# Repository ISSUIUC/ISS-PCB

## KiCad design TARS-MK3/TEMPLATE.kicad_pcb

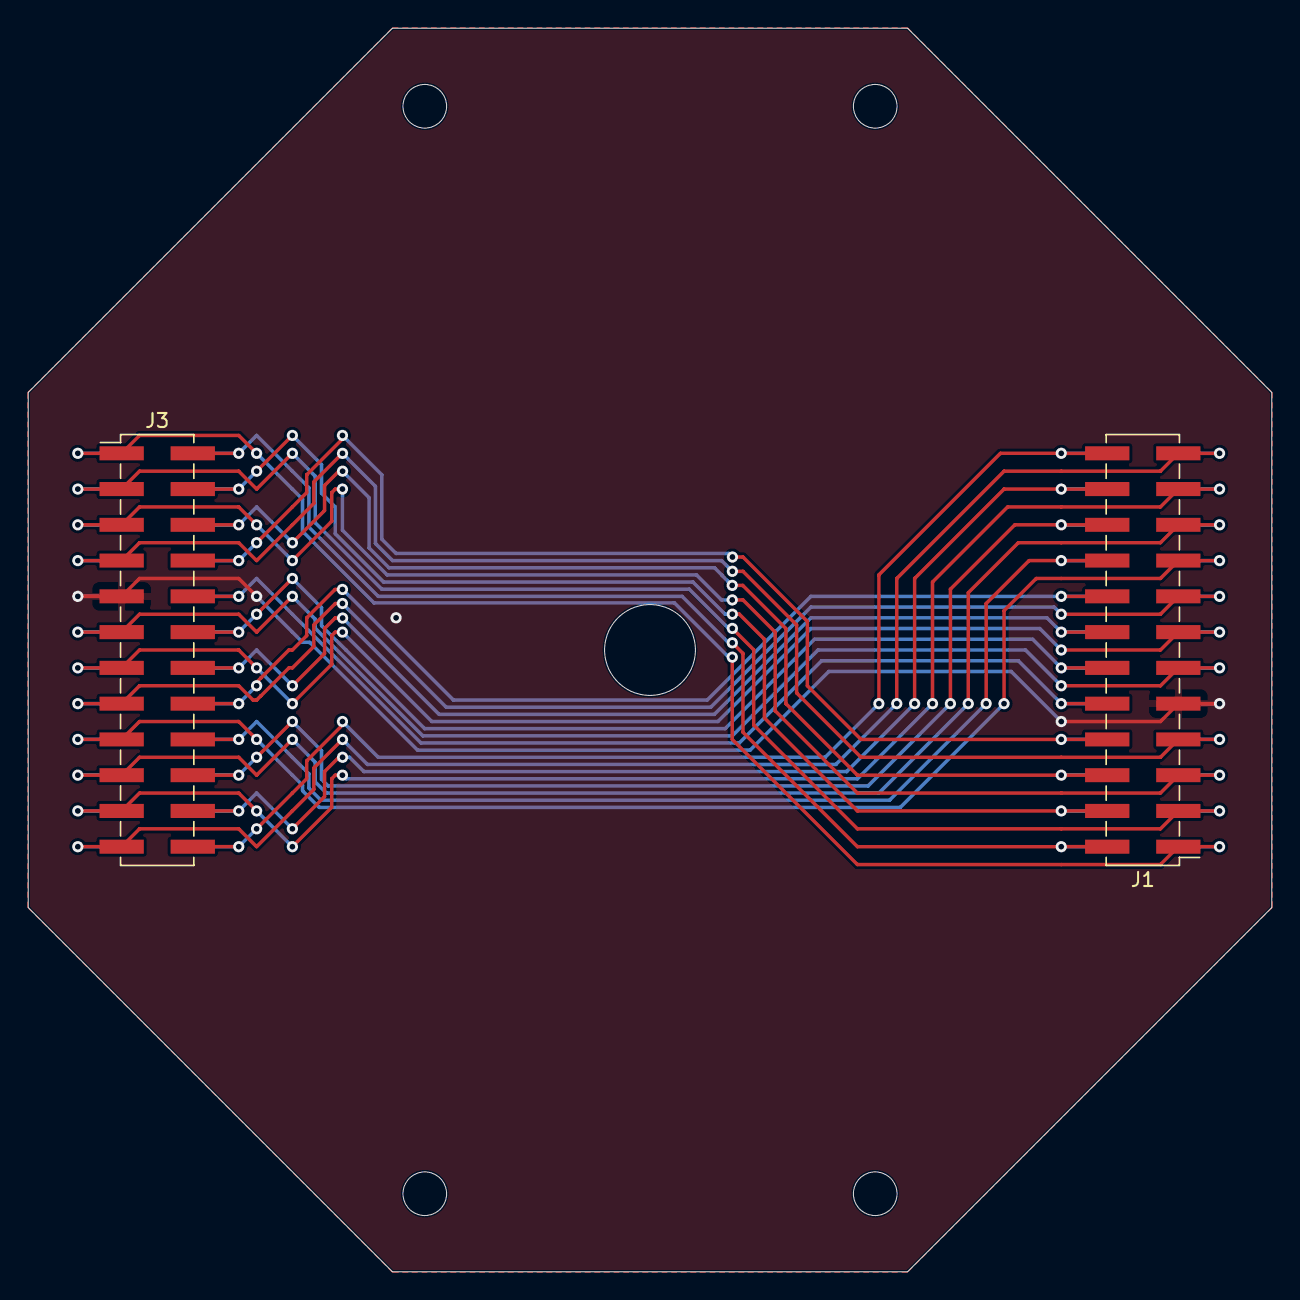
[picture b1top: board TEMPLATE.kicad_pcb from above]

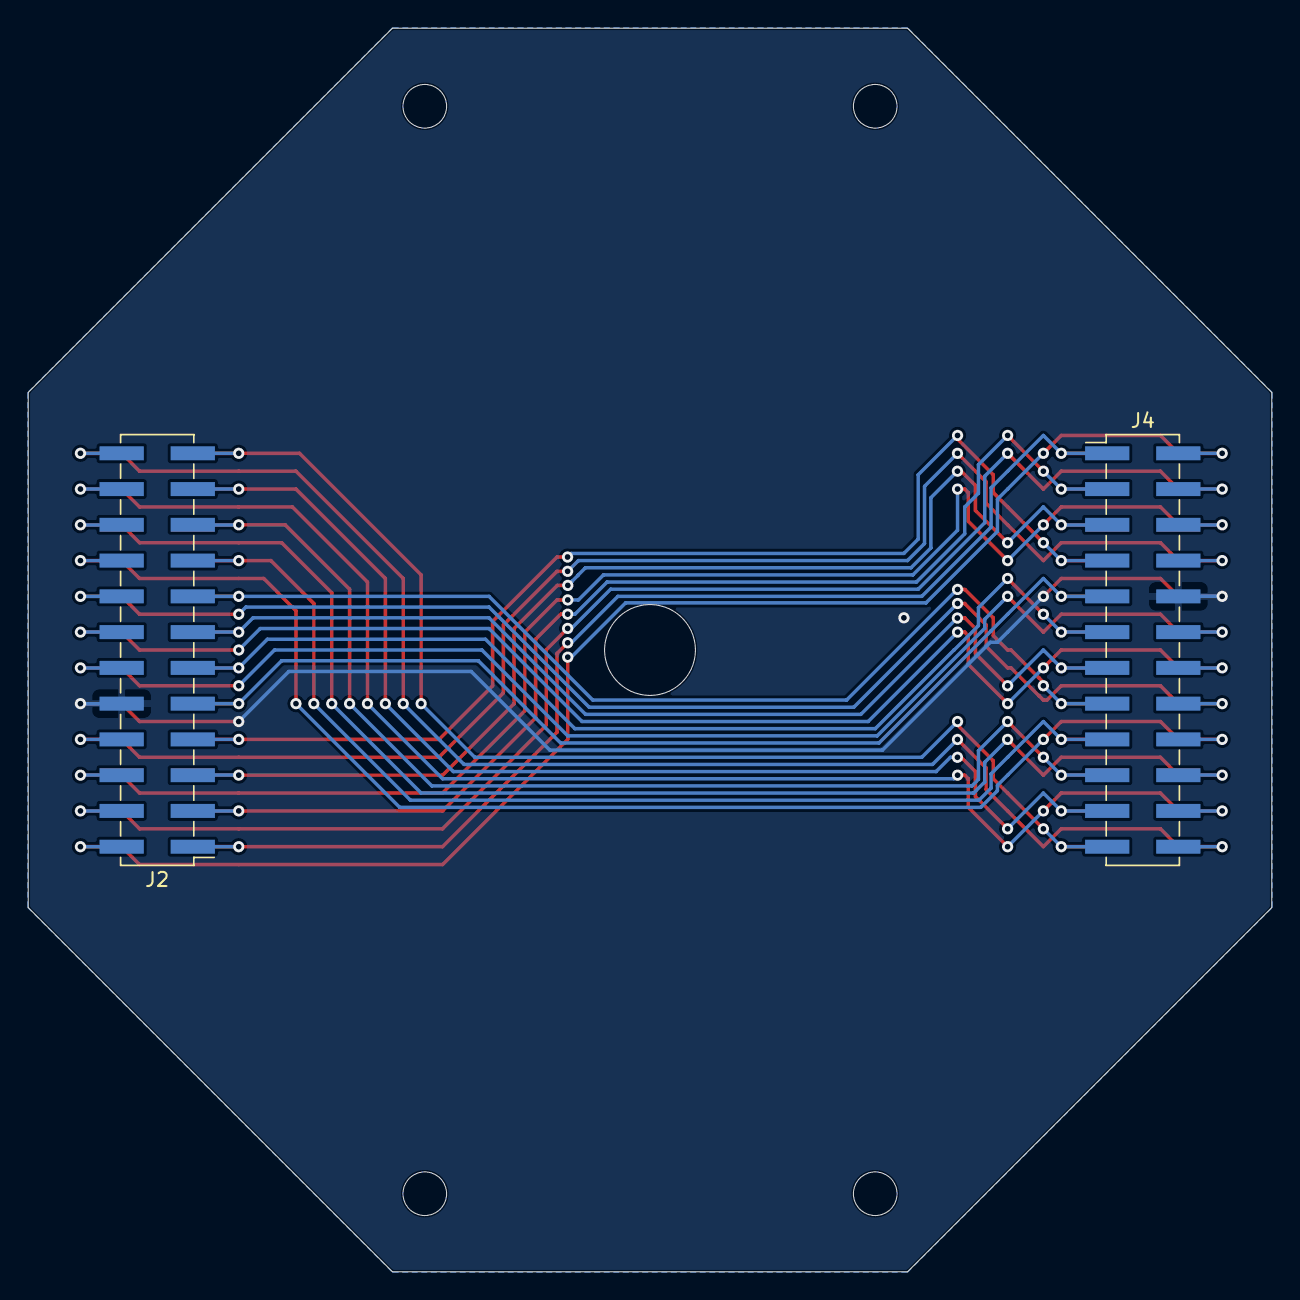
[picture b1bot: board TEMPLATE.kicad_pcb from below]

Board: 2 copper layers, 88.3 x 88.3 mm, 4 parts (2 on the bottom side), 24 nets.

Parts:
J1, J2, J3, J4: Conn_02x12_Odd_Even; PinHeader_2x12_P2.54mm_Vertical_SMD

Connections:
/3V3: J1.7, J2.8, J3.7, J4.8
/5V: J1.5, J2.6, J3.5, J4.6
/9V: J1.3, J2.4, J3.3, J4.4
/B2B_GPIO_0: J1.2, J2.1, J3.2, J4.1
/B2B_GPIO_1: J1.4, J2.3, J3.4, J4.3
/B2B_GPIO_2: J1.6, J2.5, J3.6, J4.5
/B2B_GPIO_3: J1.8, J2.7, J3.8, J4.7
/B2B_GPIO_4: J1.10, J2.9, J3.10, J4.9
/B2B_GPIO_5: J1.12, J2.11, J3.12, J4.11
/B2B_GPIO_6: J1.14, J2.13, J3.14, J4.13
/B2B_GPIO_7: J1.16, J2.15, J3.16, J4.15
/B2B_GPIO_8: J1.18, J2.17, J3.18, J4.17
/B2B_GPIO_9: J1.20, J2.19, J3.20, J4.19
/B2B_GPIO_10: J1.22, J2.21, J3.22, J4.21
/B2B_GPIO_11: J1.24, J2.23, J3.24, J4.23
/B2B_I2C_SCL: J1.17, J2.18, J3.17, J4.18
/B2B_I2C_SDA: J1.15, J2.16, J3.15, J4.16
/B2B_SPI_MISO: J1.21, J2.22, J3.21, J4.22
/B2B_SPI_MOSI: J1.23, J2.24, J3.23, J4.24
/B2B_SPI_SCK: J1.19, J2.20, J3.19, J4.20
/B2B_UART_RX: J1.11, J2.12, J3.11, J4.12
/B2B_UART_TX: J1.13, J2.14, J3.13, J4.14
/GND: J1.9, J2.10, J3.9, J4.10
/VBAT: J1.1, J2.2, J3.1, J4.2

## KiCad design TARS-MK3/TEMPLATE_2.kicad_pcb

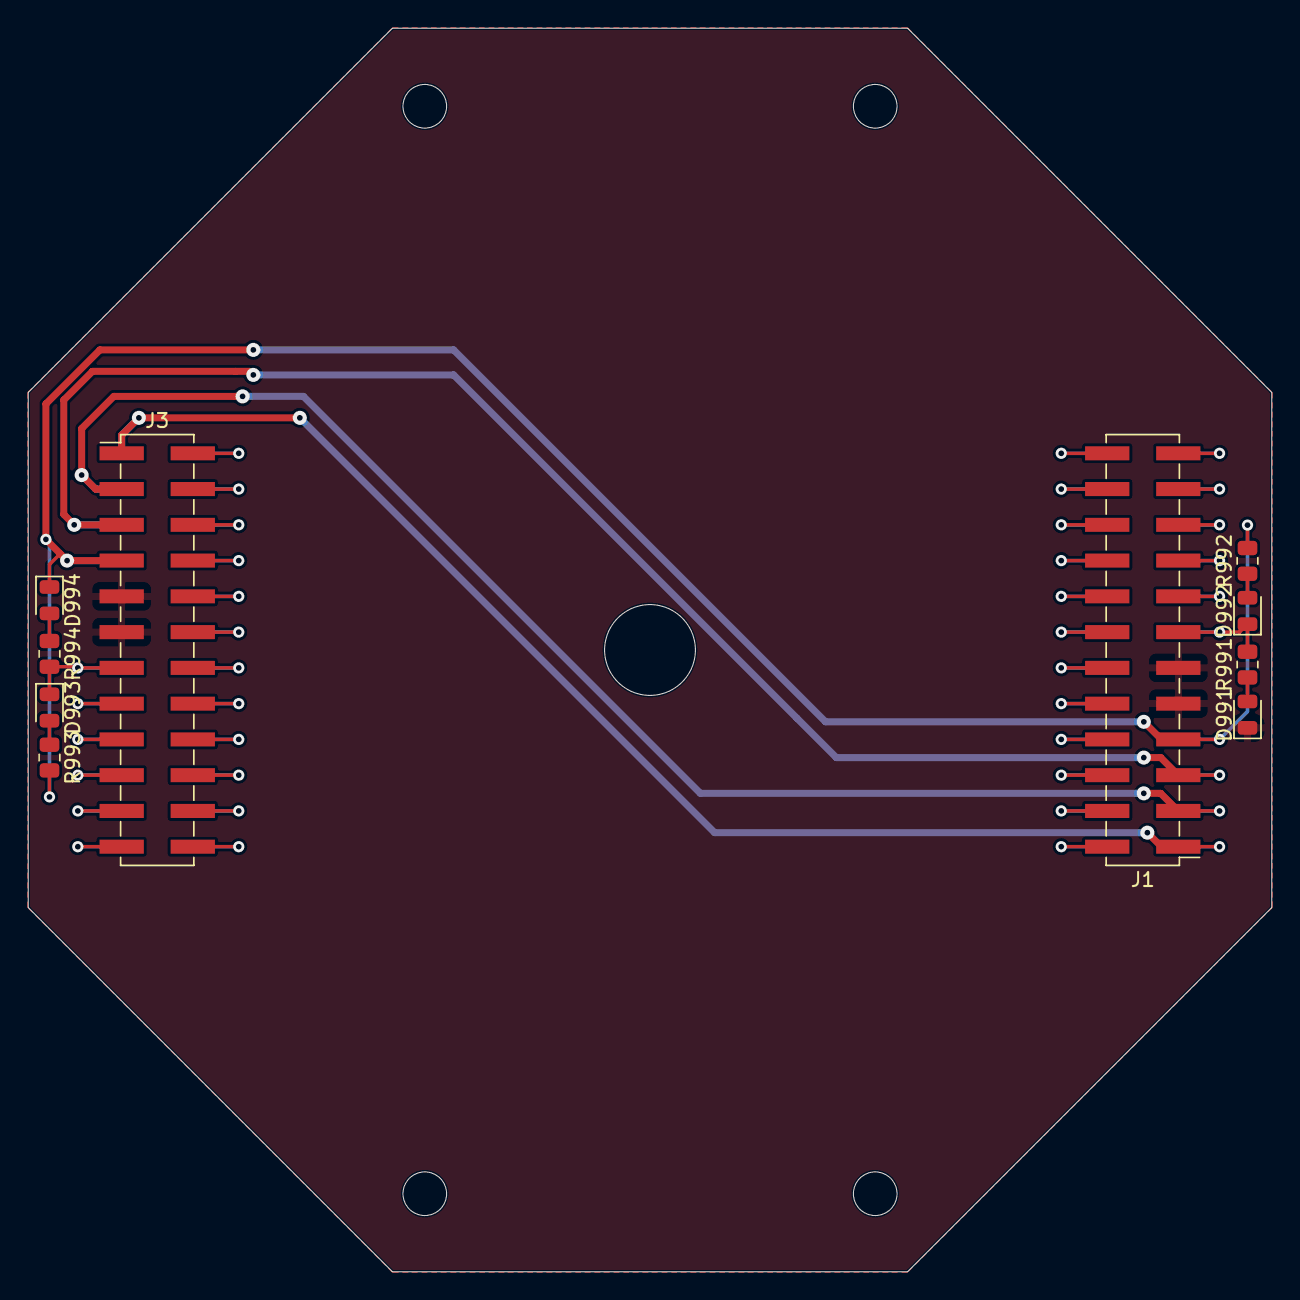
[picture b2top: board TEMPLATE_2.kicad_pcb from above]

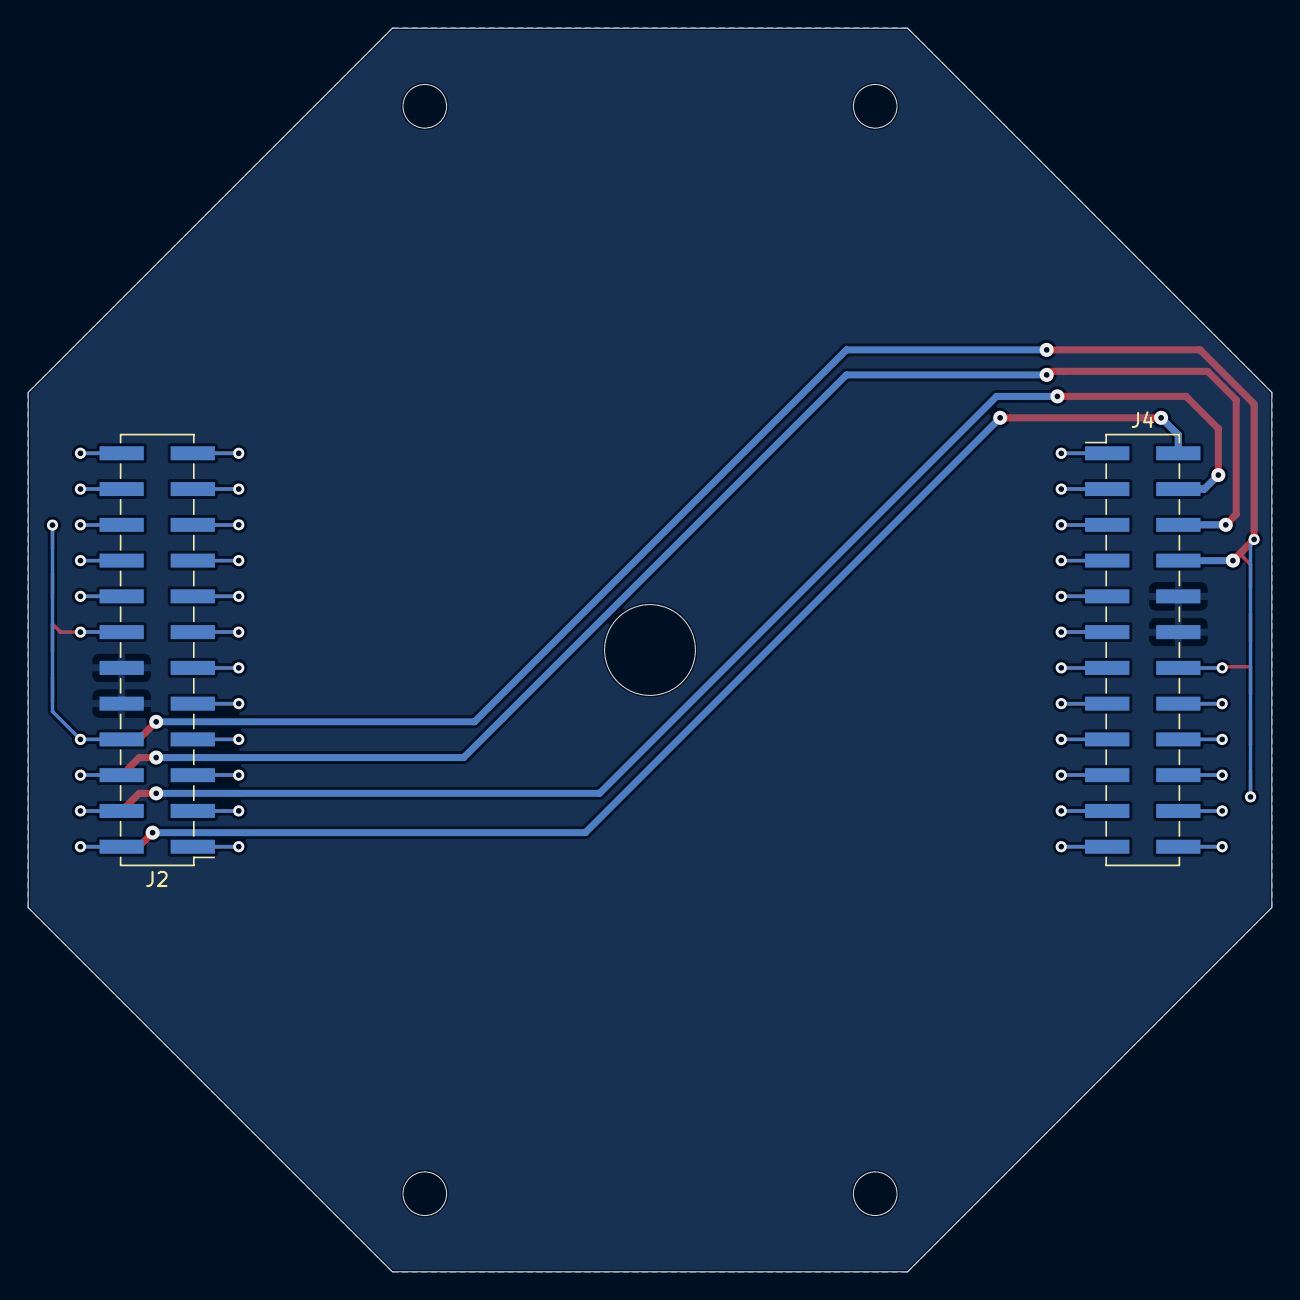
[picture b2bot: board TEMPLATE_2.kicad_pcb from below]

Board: 2 copper layers, 88.3 x 88.3 mm, 12 parts (2 on the bottom side), 45 nets.

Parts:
D991, D993: GREEN; LED_0805_2012Metric
D992, D994: RED; LED_0805_2012Metric
J1, J2, J3, J4: Conn_02x12_Odd_Even; PinHeader_2x12_P2.54mm_Vertical_SMD
R991, R992, R993, R994: 270Ohm; R_0805_2012Metric

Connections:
/3V3: D994.1 (K), J1.7, J2.8, J3.7, J4.8, R992.2, R993.2
/5V: J1.5, J2.6, J3.5, J4.6
/9V: J1.3, J2.4, J3.3, J4.4
/B2B_GPIO_0: J1.16, J2.15
/B2B_GPIO_1: J1.18, J2.17
/B2B_GPIO_2: J1.20, J2.19
/B2B_GPIO_3: J1.22, J2.21
/B2B_GPIO_4: J1.24, J2.23
/B2B_GPIO_5: J3.15, J4.16
/B2B_GPIO_6: J3.17, J4.18
/B2B_GPIO_7: J3.19, J4.20
/B2B_GPIO_8: J3.21, J4.22
/B2B_GPIO_9: J3.23, J4.24
/B2B_GPIO_10: J3.2, J4.1
/B2B_GPIO_11: J3.4, J4.3
/B2B_GPIO_12: J3.6, J4.5
/B2B_GPIO_13: J3.8, J4.7
/B2B_GPIO_14: J3.10, J4.9
/B2B_GPIO_15: J3.12, J4.11
/B2B_GPIO_16: J3.14, J4.13
/B2B_GPIO_17: J3.16, J4.15
/B2B_GPIO_18: J3.18, J4.17
/B2B_GPIO_19: J3.20, J4.19
/B2B_GPIO_20: J3.22, J4.21
/B2B_GPIO_21: J3.24, J4.23
/B2B_I2C_SCL: J1.21, J2.22
/B2B_I2C_SDA: J1.23, J2.24
/B2B_SPI_MISO: J1.19, J2.20
/B2B_SPI_MOSI: J1.17, J2.18
/B2B_SPI_SCK: J1.15, J2.16
/B2B_UART_SDI: J1.2, J2.1
/B2B_UART_SDO: J1.4, J2.3
/CONT_3V3: D992.1 (K), J1.13, J2.14, R991.2
/CONT_GND: D993.1 (K), J3.13, J4.14, R994.2
/GND: D991.1 (K), J1.9, J1.11, J2.10, J2.12, J3.9, J3.11, J4.10, J4.12
/POWER_RESET: J1.14, J2.13
/POWER_STATE: J1.12, J2.11
/TELEM_CS: J1.6, J2.5
/TELEM_INT: J1.8, J2.7
/TELEM_RST: J1.10, J2.9
/VBAT: J1.1, J2.2, J3.1, J4.2
unnamed: D991.2 (A), R991.1
unnamed: D992.2 (A), R992.1
unnamed: D993.2 (A), R993.1
unnamed: D994.2 (A), R994.1

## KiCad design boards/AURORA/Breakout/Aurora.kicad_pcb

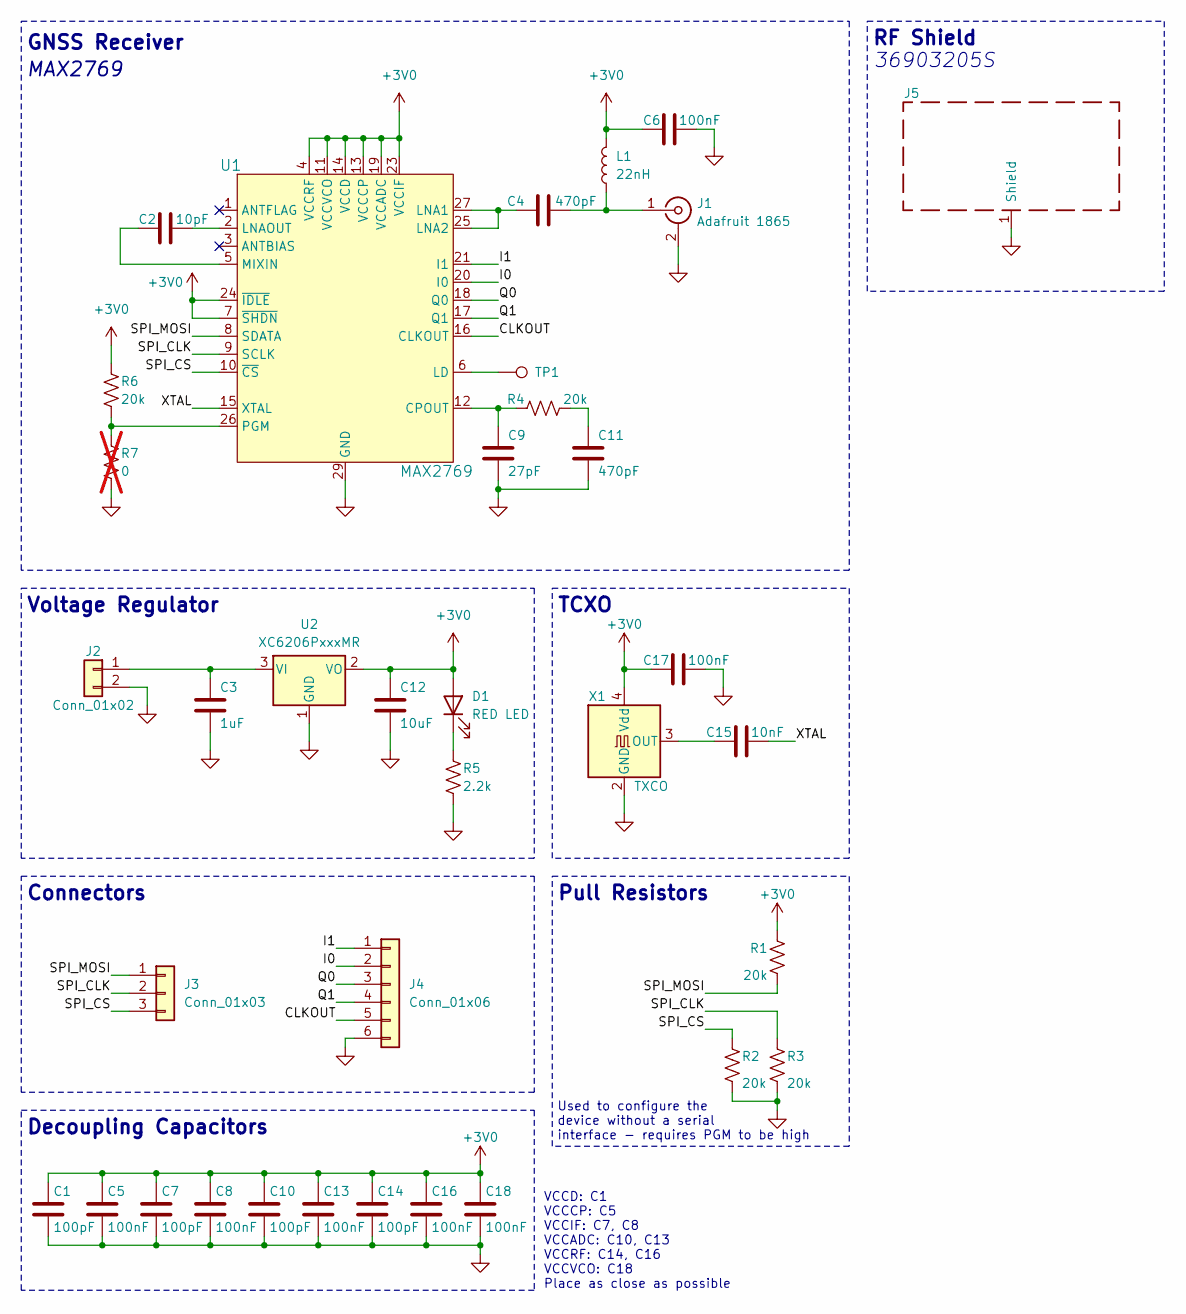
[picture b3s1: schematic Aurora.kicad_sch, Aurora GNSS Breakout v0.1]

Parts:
C1, C7, C10, C14: 100pF; C_0603_1608Metric
C2: 10pF; C_0603_1608Metric
C3: 1uF; C_0603_1608Metric
C4, C11: 470pF; C_0603_1608Metric
C5, C6, C8, C13, C16, C17, C18: 100nF; C_0603_1608Metric
C9: 27pF; C_0603_1608Metric
C12: 10uF; C_0603_1608Metric
C15: 10nF; C_0603_1608Metric
D1: RED LED; LED_0603_1608Metric
J1: Adafruit 1865; SMA_Molex_73251-2120_EdgeMount_Horizontal
J2: Conn_01x02; JST_PH_S2B-PH-K_1x02_P2.00mm_Horizontal
J3: Conn_01x03; PinHeader_1x03_P2.54mm_Vertical
J4: Conn_01x06; PinHeader_1x06_P2.54mm_Vertical
J5: RFShield_OnePiece; Wuerth_36103205_20x20mm
L1: 22nH; L_0603_1608Metric
R1, R2, R3, R4, R6: 20k; R_0603_1608Metric
R5: 2.2k; R_0603_1608Metric
R7: 0; R_0603_1608Metric; not fitted
TP1: TestPoint; TestPoint_Pad_D1.0mm
U1: MAX2769; QFN-28-1EP_5x5mm_P0.5mm_EP3.35x3.35mm_ThermalVias
U2: XC6206PxxxMR; SOT-23-3
X1: TXCO; Oscillator_SMD_Abracon_ASE-4Pin_3.2x2.5mm

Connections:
+3V0: C1.1, C5.1, C6.2, C7.1, C8.1, C10.1, C12.1, C13.1, C14.1, C16.1, C17.2, C18.1, D1.2 (A), L1.2, R1.2, R6.1, U1.4 (VCCRF), U1.7 (~SHDN), U1.11 (VCCVCO), U1.13 (VCCCP), U1.14 (VCCD), U1.19 (VCCADC), U1.23 (VCCIF), U1.24 (~IDLE), U2.2 (VO), X1.4 (Vdd)
/CLKOUT: J4.5, U1.16 (CLKOUT)
/I0: J4.2, U1.20 (I0)
/I1: J4.1, U1.21 (I1)
/Q0: J4.3, U1.18 (Q0)
/Q1: J4.4, U1.17 (Q1)
/SPI_CLK: J3.2, R3.2, U1.9 (SCLK)
/SPI_CS: J3.3, R2.2, U1.10 (~CS)
/SPI_MOSI: J3.1, R1.1, U1.8 (SDATA)
/XTAL: C15.1, U1.15 (XTAL)
GND: C1.2, C3.2, C5.2, C6.1, C7.2, C8.2, C9.1, C10.2, C11.2, C12.2, C13.2, C14.2, C16.2, C17.1, C18.2, J1.2 (Ext), J2.2, J4.6, J5.1 (Shield), R2.1, R3.1, R5.2, R7.2, U1.29 (GND), U2.1 (GND), X1.2 (GND)
unnamed: C11.1, R4.2
unnamed: D1.1 (K), R5.1
unnamed: C4.2, J1.1 (In), L1.1
unnamed: C3.1, J2.1, U2.3 (VI)
unnamed: C9.2, R4.1, U1.12 (CPOUT)
unnamed: TP1.1, U1.6 (LD)
unnamed: C4.1, U1.25 (LNA2), U1.27 (LNA1)
unnamed: C2.2, U1.2 (LNAOUT)
unnamed: C2.1, U1.5 (MIXIN)
unnamed: R6.2, R7.1, U1.26 (PGM)
unnamed: C15.2, X1.3 (OUT)

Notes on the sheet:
MAX2769
GNSS Receiver
Pull Resistors
Decoupling Capacitors
RF Shield
Used to configure the device without a serial interface - requires PGM to be high
Voltage Regulator
TCXO
36903205S
VCCD: C1 VCCCP: C5 VCCIF: C7, C8 VCCADC: C10, C13 VCCRF: C14, C16 VCCVCO: C18 Place as close as possible
Connectors

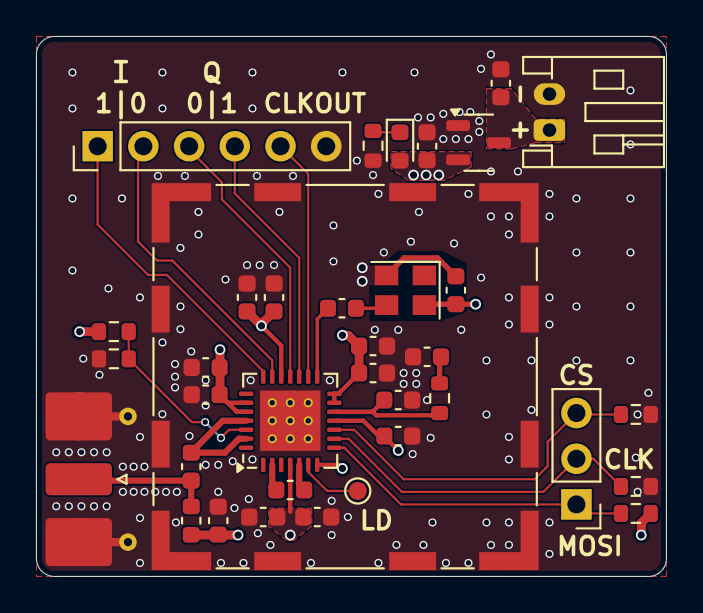
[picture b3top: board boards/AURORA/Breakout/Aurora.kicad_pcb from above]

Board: 4 copper layers, 35.0 x 30.0 mm, 36 parts (0 on the bottom side), 22 nets.

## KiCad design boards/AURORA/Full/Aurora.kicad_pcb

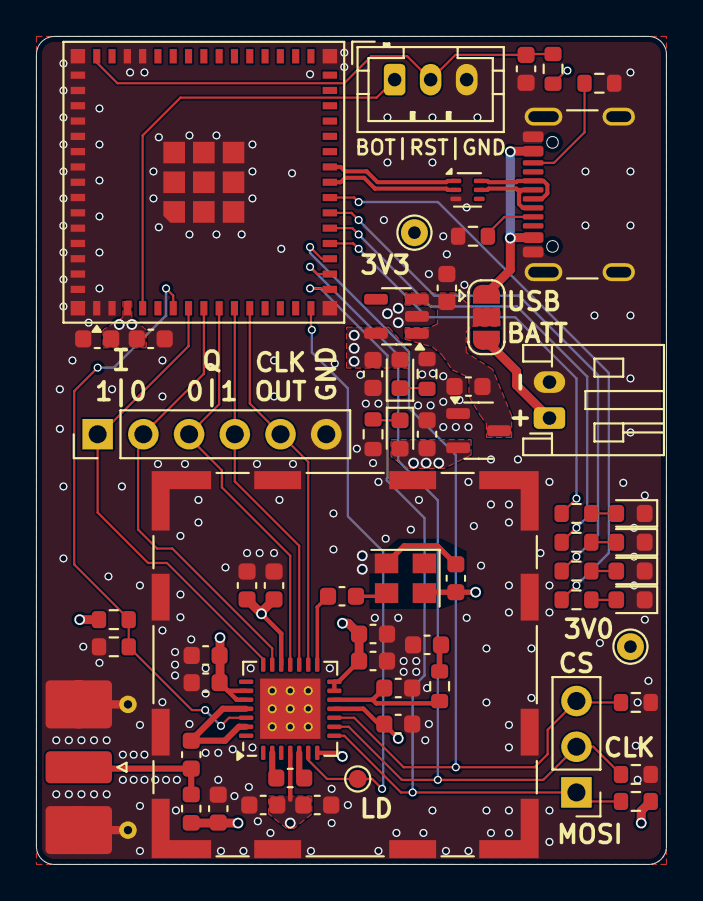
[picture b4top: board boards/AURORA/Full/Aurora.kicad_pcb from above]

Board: 4 copper layers, 35.0 x 46.0 mm, 62 parts (0 on the bottom side), 42 nets.

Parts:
C1, C7, C10, C14: 100pF; C_0603_1608Metric
C2: 10pF; C_0603_1608Metric
C3, C22, C23: 1uF; C_0603_1608Metric
C4, C11: 470pF; C_0603_1608Metric
C5, C6, C8, C13, C16, C17, C18, C21: 100nF; C_0603_1608Metric
C9: 27pF; C_0603_1608Metric
C12: 10uF; C_0603_1608Metric
C15: 10nF; C_0603_1608Metric
C19: 22uF; C_0603_1608Metric
C20: 0.1uF; C_0603_1608Metric
D1, D4: ORANGE LED; LED_0603_1608Metric
D2, D3: RED LED; LED_0603_1608Metric
D5: GREEN LED; LED_0603_1608Metric
D6: BLUE LED; LED_0603_1608Metric
J1: Adafruit 1865; SMA_Molex_73251-2120_EdgeMount_Horizontal
J2: Conn_01x02; JST_PH_S2B-PH-K_1x02_P2.00mm_Horizontal
J3: Conn_01x03; PinHeader_1x03_P2.54mm_Vertical
J4: Conn_01x06; PinHeader_1x06_P2.54mm_Vertical
J5: RFShield_OnePiece; Wuerth_36103205_20x20mm
J6: USB4105-GF-A; USB_C_Receptacle_GCT_USB4105-xx-A_16P_TopMnt_Horizontal
J7: Conn_01x03; JST_PH_B3B-PH-K_1x03_P2.00mm_Vertical
JP1: Jumper_3_Open; SolderJumper-3_P1.3mm_Open_RoundedPad1.0x1.5mm
L1: 22nH; L_0603_1608Metric
R1, R2, R3, R4, R6, R11: 20k; R_0603_1608Metric
R5, R10: 2.2k; R_0603_1608Metric
R7: 0; R_0603_1608Metric
R8, R9: 5.1k; R_0603_1608Metric
R12, R13, R14, R15: 470; R_0603_1608Metric
TP1: TestPoint; TestPoint_Pad_D1.0mm
TP2, TP3: TestPoint; TestPoint_THTPad_D1.5mm_Drill0.7mm
U1: MAX2769; QFN-28-1EP_5x5mm_P0.5mm_EP3.35x3.35mm_ThermalVias
U2: XC6206PxxxMR; SOT-23-3
U3: ESP32-S3-MINI-1U; ESP32-S2-MINI-1U
U4: ECMF02-2AMX6; ST_UQFN-6L_1.5x1.7mm_P0.5mm
U5: TLV73333PDBV; SOT-23-5
X1: TXCO; Oscillator_SMD_Abracon_ASE-4Pin_3.2x2.5mm

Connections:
+3V0: C1.1, C5.1, C6.2, C7.1, C8.1, C10.1, C12.1, C13.1, C14.1, C16.1, C17.2, C18.1, D1.2 (A), L1.2, R1.2, R6.1, TP2.1, U1.4 (VCCRF), U1.7 (~SHDN), U1.11 (VCCVCO), U1.13 (VCCCP), U1.14 (VCCD), U1.19 (VCCADC), U1.23 (VCCIF), U1.24 (~IDLE), U2.2 (VO), X1.4 (Vdd)
+3V3: C19.2, C20.2, C22.1, D2.2 (A), R11.2, TP3.1, U3.3 (3V3), U5.5 (OUT)
/BOOT_SW: J7.1, U3.4 (IO0)
/CLKOUT: J4.5, U1.16 (CLKOUT), U3.11 (IO7)
/D+: J6.A6 (D+), J6.B6 (D+), U4.6 (D+_out)
/D-: J6.A7 (D-), J6.B7 (D-), U4.5 (D-_out)
/I0: J4.2, U1.20 (I0), U3.8 (IO4)
/I1: J4.1, U1.21 (I1), U3.7 (IO3)
/LD: TP1.1, U1.6 (LD), U3.15 (IO11)
/LED_BLUE: R15.1, U3.19 (IO15)
/LED_GREEN: R14.1, U3.20 (IO16)
/LED_ORANGE: R13.1, U3.21 (IO17)
/LED_RED: R12.1, U3.22 (IO18)
/PGM: R6.2, R7.1, U1.26 (PGM), U3.6 (IO2)
/Q0: J4.3, U1.18 (Q0), U3.9 (IO5)
/Q1: J4.4, U1.17 (Q1), U3.10 (IO6)
/RESET_SW: C23.1, J7.2, R11.1, U3.45 (EN)
/SPI_CLK: J3.2, R3.2, U1.9 (SCLK), U3.17 (IO13)
/SPI_CS: J3.3, R2.2, U1.10 (~CS), U3.18 (IO14)
/SPI_MOSI: J3.1, R1.1, U1.8 (SDATA), U3.16 (IO12)
/USB_D+: U3.24 (IO20), U4.1 (D+_in)
/USB_D-: U3.23 (IO19), U4.2 (D-_in)
/VBAT: J2.1, JP1.3 (B)
/VBUS: J6.A4 (VBUS), J6.A9 (VBUS), J6.B4 (VBUS), J6.B9 (VBUS), JP1.1 (A)
/VSYS: C3.1, C21.1, JP1.2 (C), U2.3 (VI), U5.1 (IN), U5.3 (EN)
/XTAL: C15.1, U1.15 (XTAL)
GND: C1.2, C3.2, C5.2, C6.1, C7.2, C8.2, C9.1, C10.2, C11.2, C12.2, C13.2, C14.2, C16.2, C17.1, C18.2, C19.1, C20.1, C21.2, C22.2, C23.2, D3.1 (K), D4.1 (K), D5.1 (K), D6.1 (K), J1.2 (Ext), J2.2, J4.6, J5.1 (Shield), J6.A1 (GND), J6.A12 (GND), J6.B1 (GND), J6.B12 (GND), J6.S1 (SHIELD), J7.3, R2.1, R3.1, R5.1, R7.2, R8.2, R9.2, R10.1, U1.29 (GND), U2.1 (GND), U3.1 (GND), U3.2 (GND), U3.42 (GND), U3.43 (GND), U3.46 (GND), U3.47 (GND), U3.48 (GND), U3.49 (GND), U3.50 (GND), U3.51 (GND), U3.52 (GND), U3.53 (GND), U3.54 (GND), U3.55 (GND), U3.56 (GND), U3.57 (GND), U3.58 (GND), U3.59 (GND), U3.60 (GND), U3.61 (GND), U3.62 (GND), U3.63 (GND), U3.64 (GND), U3.65 (GND), U4.3 (GND), U5.2 (GND), X1.2 (GND)
unnamed: C11.1, R4.2
unnamed: D1.1 (K), R5.2
unnamed: D2.1 (K), R10.2
unnamed: D3.2 (A), R12.2
unnamed: D4.2 (A), R13.2
unnamed: D5.2 (A), R14.2
unnamed: D6.2 (A), R15.2
unnamed: C4.2, J1.1 (In), L1.1
unnamed: J6.A5 (CC1), R8.1
unnamed: J6.B5 (CC2), R9.1
unnamed: C9.2, R4.1, U1.12 (CPOUT)
unnamed: C4.1, U1.25 (LNA2), U1.27 (LNA1)
unnamed: C2.2, U1.2 (LNAOUT)
unnamed: C2.1, U1.5 (MIXIN)
unnamed: C15.2, X1.3 (OUT)

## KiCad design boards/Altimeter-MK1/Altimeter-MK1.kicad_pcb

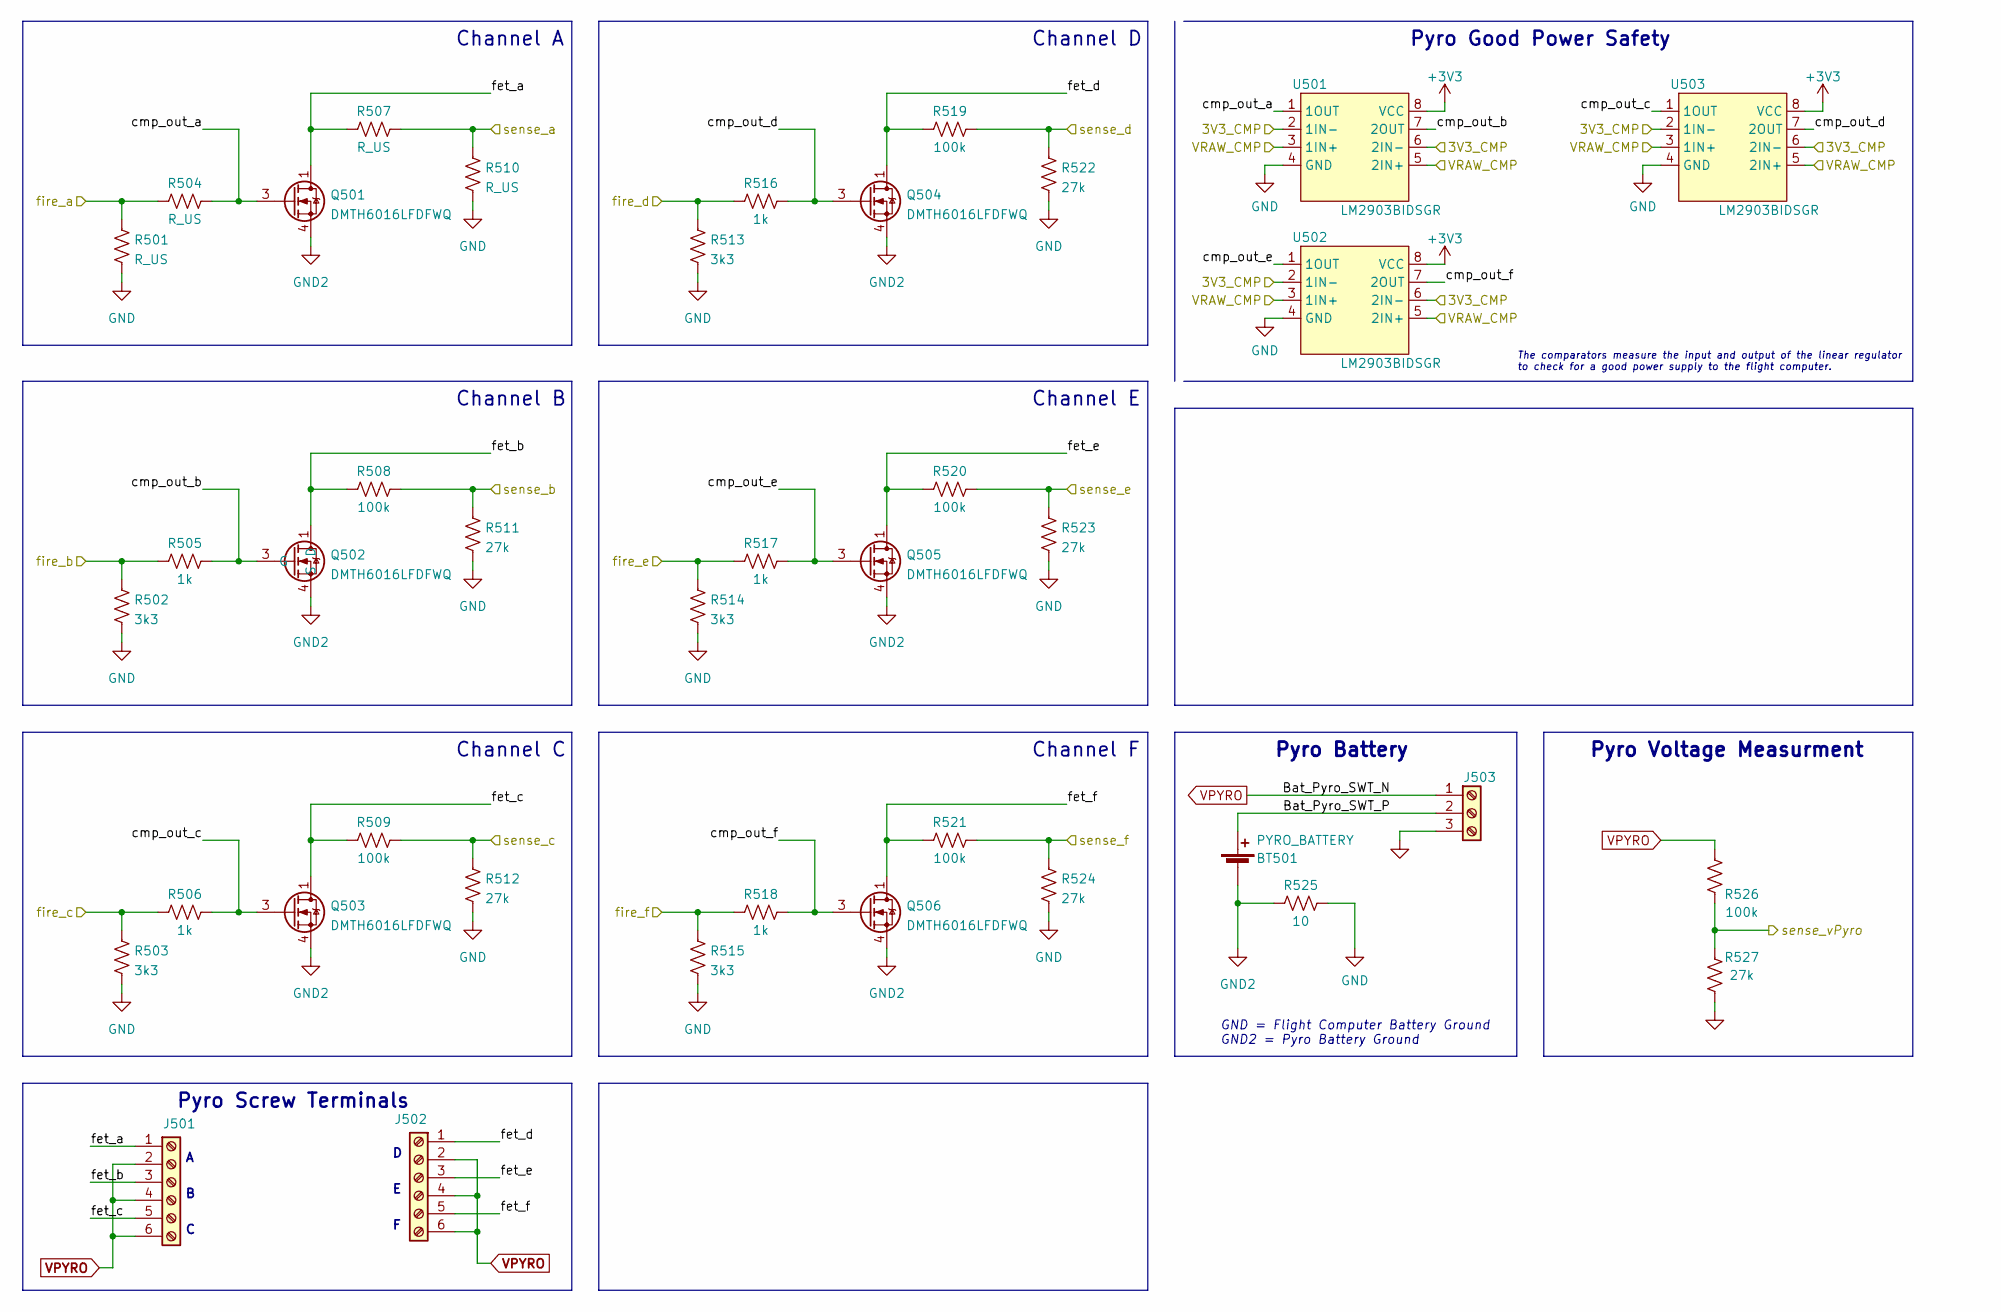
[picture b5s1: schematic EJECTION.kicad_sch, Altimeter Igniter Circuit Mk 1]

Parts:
BT501: PYRO_BATTERY; JST_PH_B2B-PH-K_1x02_P2.00mm_Vertical
J501, J502: Screw_Terminal_01x06; TE_1776113-6
J503: TE_1776113-3
Q501, Q502, Q503, Q504, Q505, Q506: DMTH6016LFDFWQ; Diodes_UDFN2020-6_Type-F
R501, R504, R507, R510: R_US; R_0603_1608Metric
R502, R503, R513, R514, R515: 3k3; R_0603_1608Metric
R505, R506, R516, R517, R518: 1k; R_0603_1608Metric
R508, R509, R519, R520, R521, R526: 100k; R_0603_1608Metric
R511, R512, R522, R523, R524, R527: 27k; R_0603_1608Metric
R525: 10; R_0603_1608Metric
U501, U502, U503: LM2903BIDSGR; WSON-8-1EP_2x2mm_P0.5mm_EP0.9x1.6mm

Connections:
/EJECTION/3V3_CMP: U501.2 (1IN-), U501.6 (2IN-), U502.2 (1IN-), U502.6 (2IN-), U503.2 (1IN-), U503.6 (2IN-); also elsewhere on the board
/EJECTION/Bat_Pyro_SWT_P: BT501.1 (+), J503.2
/EJECTION/VRAW_CMP: U501.3 (1IN+), U501.5 (2IN+), U502.3 (1IN+), U502.5 (2IN+), U503.3 (1IN+), U503.5 (2IN+); also elsewhere on the board
/EJECTION/cmp_out_a: Q501.3 (G), R504.2, U501.1 (1OUT)
/EJECTION/cmp_out_b: Q502.3 (G), R505.2, U501.7 (2OUT)
/EJECTION/cmp_out_c: Q503.3 (G), R506.2, U503.1 (1OUT)
/EJECTION/cmp_out_d: Q504.3 (G), R516.2, U503.7 (2OUT)
/EJECTION/cmp_out_e: Q505.3 (G), R517.2, U502.1 (1OUT)
/EJECTION/cmp_out_f: Q506.3 (G), R518.2, U502.7 (2OUT)
/EJECTION/fet_a: J501.1, Q501.1 (D), Q501.2 (D), Q501.5 (D), Q501.6 (D), Q501.7 (D), R507.1
/EJECTION/fet_b: J501.3, Q502.1 (D), Q502.2 (D), Q502.5 (D), Q502.6 (D), Q502.7 (D), R508.1
/EJECTION/fet_c: J501.5, Q503.1 (D), Q503.2 (D), Q503.5 (D), Q503.6 (D), Q503.7 (D), R509.1
/EJECTION/fet_d: J502.1, Q504.1 (D), Q504.2 (D), Q504.5 (D), Q504.6 (D), Q504.7 (D), R519.1
/EJECTION/fet_e: J502.3, Q505.1 (D), Q505.2 (D), Q505.5 (D), Q505.6 (D), Q505.7 (D), R520.1
/EJECTION/fet_f: J502.5, Q506.1 (D), Q506.2 (D), Q506.5 (D), Q506.6 (D), Q506.7 (D), R521.1
/EJECTION/fire_a: R501.1, R504.1; also elsewhere on the board
/EJECTION/fire_b: R502.1, R505.1; also elsewhere on the board
/EJECTION/fire_c: R503.1, R506.1; also elsewhere on the board
/EJECTION/fire_d: R513.1, R516.1; also elsewhere on the board
/EJECTION/fire_e: R514.1, R517.1; also elsewhere on the board
/EJECTION/fire_f: R515.1, R518.1; also elsewhere on the board
/EJECTION/sense_a: R507.2, R510.1
/EJECTION/sense_b: R508.2, R511.1
/EJECTION/sense_c: R509.2, R512.1
/EJECTION/sense_d: R519.2, R522.1
/EJECTION/sense_e: R520.2, R523.1
/EJECTION/sense_f: R521.2, R524.1
/EJECTION/sense_vPyro: R526.1, R527.1; also elsewhere on the board
GND2: BT501.2 (-), Q501.4 (S), Q501.8 (S), Q502.4 (S), Q502.8 (S), Q503.4 (S), Q503.8 (S), Q504.4 (S), Q504.8 (S), Q505.4 (S), Q505.8 (S), Q506.4 (S), Q506.8 (S), R525.1
VPYRO: J501.2, J501.4, J501.6, J502.2, J502.4, J502.6, J503.1, R526.2

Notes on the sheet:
Pyro Screw Terminals
Channel D
Pyro Good Power Safety
The comparators measure the input and output of the linear regulator to check for a good power supply to the flight computer.
Channel F
Channel A
GND = Flight Computer Battery Ground GND2 = Pyro Battery Ground
Channel B
Channel C
Pyro Voltage Measurment
Channel E
Pyro Battery

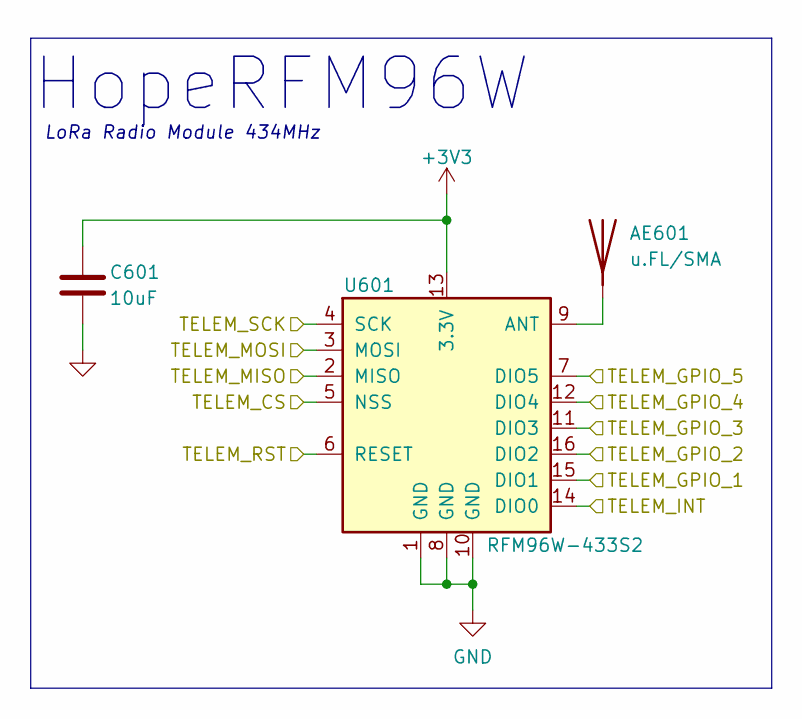
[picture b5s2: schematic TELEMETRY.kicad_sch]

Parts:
AE601: u.FL/SMA; SMA_Molex_73251-1153_EdgeMount_Horizontal
C601: 10uF; C_0805_2012Metric
U601: RFM96W-433S2; HOPERF_RFM9XW_SMD

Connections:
/MCU/TELEM_CS: U601.5 (NSS); also elsewhere on the board
/MCU/TELEM_GPIO_1: U601.15 (DIO1); also elsewhere on the board
/MCU/TELEM_GPIO_2: U601.16 (DIO2); also elsewhere on the board
/MCU/TELEM_GPIO_3: U601.11 (DIO3); also elsewhere on the board
/MCU/TELEM_GPIO_4: U601.12 (DIO4); also elsewhere on the board
/MCU/TELEM_GPIO_5: U601.7 (DIO5); also elsewhere on the board
/MCU/TELEM_INT: U601.14 (DIO0); also elsewhere on the board
/MCU/TELEM_MISO: U601.2 (MISO); also elsewhere on the board
/MCU/TELEM_MOSI: U601.3 (MOSI); also elsewhere on the board
/MCU/TELEM_RST: U601.6 (RESET); also elsewhere on the board
/MCU/TELEM_SCK: U601.4 (SCK); also elsewhere on the board
unnamed: AE601.1 (A), U601.9 (ANT)

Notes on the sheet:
HopeRFM96W
LoRa Radio Module 434MHz
